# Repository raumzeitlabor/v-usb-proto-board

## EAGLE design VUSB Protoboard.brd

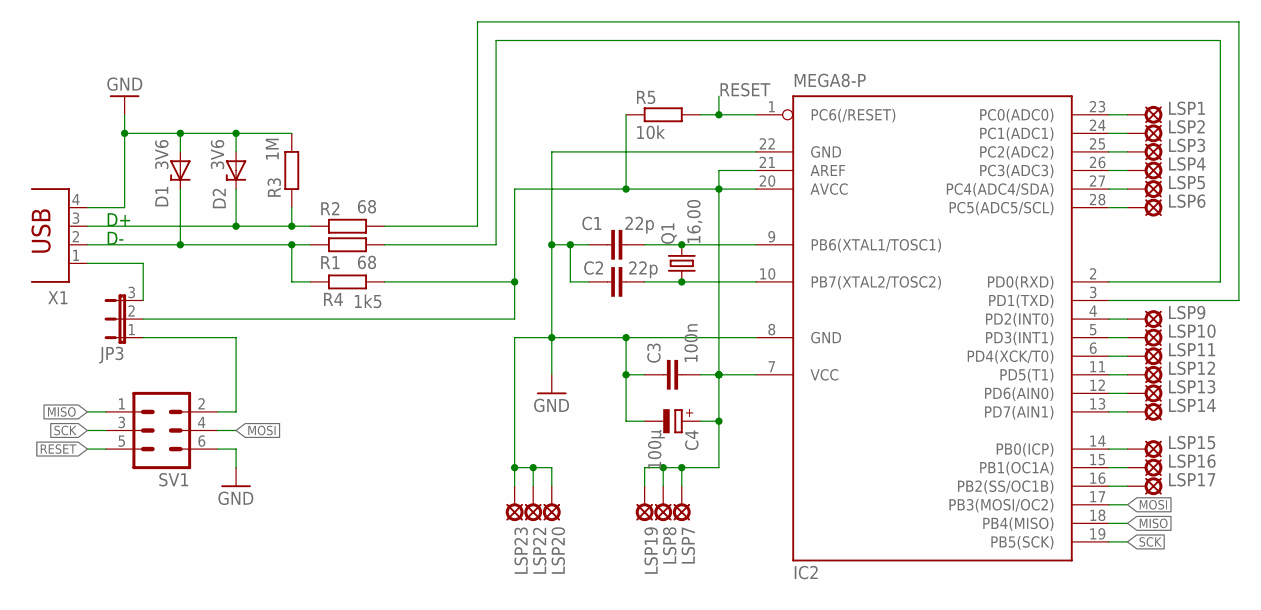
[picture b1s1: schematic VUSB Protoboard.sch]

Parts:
C1, C2: 22p; C025-025X050
C3: 100n; C025-025X050
C4: 100µ; E2,5-6
D1, D2: 3V6; ZDIO-7.5
IC2: MEGA8-P; DIL28-3
JP3: JP2E; JP2
LSP1, LSP2, LSP3, LSP4, LSP5, LSP6, LSP7, LSP8, LSP9, LSP10, LSP11, LSP12, LSP13, LSP14, LSP15, LSP16, LSP17, LSP19, LSP20, LSP22, LSP23: LSP11
Q1: 16,00; HC49/S
R1, R2: 68; 0207/10
R3: 1M; 0207/10
R4: 1k5; 0207/10
R5: 10k; 0207/10
SV1: ML6
X1: PN61729

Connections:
D+: D2.C, R2.1, R3.1, X1.3
D-: D1.C, R1.1, R4.2, X1.2
GND: C1.1, C2.1, C3.1, C4.-, D1.A, D2.A, IC2.8 (GND), IC2.22 (GND), LSP20.MP, LSP22.MP, LSP23.MP, R3.2, SV1.6, X1.4
ISPVCC: JP3.1, SV1.2
MISO: IC2.18 (PB4(MISO)), SV1.1
MOSI: IC2.17 (PB3(MOSI/OC2)), SV1.4
unnamed: IC2.2 (PD0(RXD)), R1.2
unnamed: IC2.3 (PD1(TXD)), R2.2
unnamed: JP3.3, X1.1
unnamed: IC2.16 (PB2(SS/OC1B)), LSP17.MP
unnamed: IC2.15 (PB1(OC1A)), LSP16.MP
unnamed: IC2.14 (PB0(ICP)), LSP15.MP
unnamed: IC2.13 (PD7(AIN1)), LSP14.MP
unnamed: IC2.12 (PD6(AIN0)), LSP13.MP
unnamed: C1.2, IC2.9 (PB6(XTAL1/TOSC1)), Q1.2
unnamed: C2.2, IC2.10 (PB7(XTAL2/TOSC2)), Q1.1
unnamed: IC2.11 (PD5(T1)), LSP12.MP
unnamed: IC2.6 (PD4(XCK/T0)), LSP11.MP
unnamed: IC2.5 (PD3(INT1)), LSP10.MP
unnamed: IC2.4 (PD2(INT0)), LSP9.MP
unnamed: IC2.23 (PC0(ADC0)), LSP1.MP
unnamed: IC2.24 (PC1(ADC1)), LSP2.MP
unnamed: IC2.25 (PC2(ADC2)), LSP3.MP
unnamed: IC2.26 (PC3(ADC3)), LSP4.MP
unnamed: IC2.27 (PC4(ADC4/SDA)), LSP5.MP
unnamed: IC2.28 (PC5(ADC5/SCL)), LSP6.MP
RESET: IC2.1 (PC6(/RESET)), R5.2, SV1.5
SCK: IC2.19 (PB5(SCK)), SV1.3
VCC: C3.2, C4.+, IC2.7 (VCC), IC2.20 (AVCC), IC2.21 (AREF), JP3.2, LSP7.MP, LSP8.MP, LSP19.MP, R4.1, R5.1

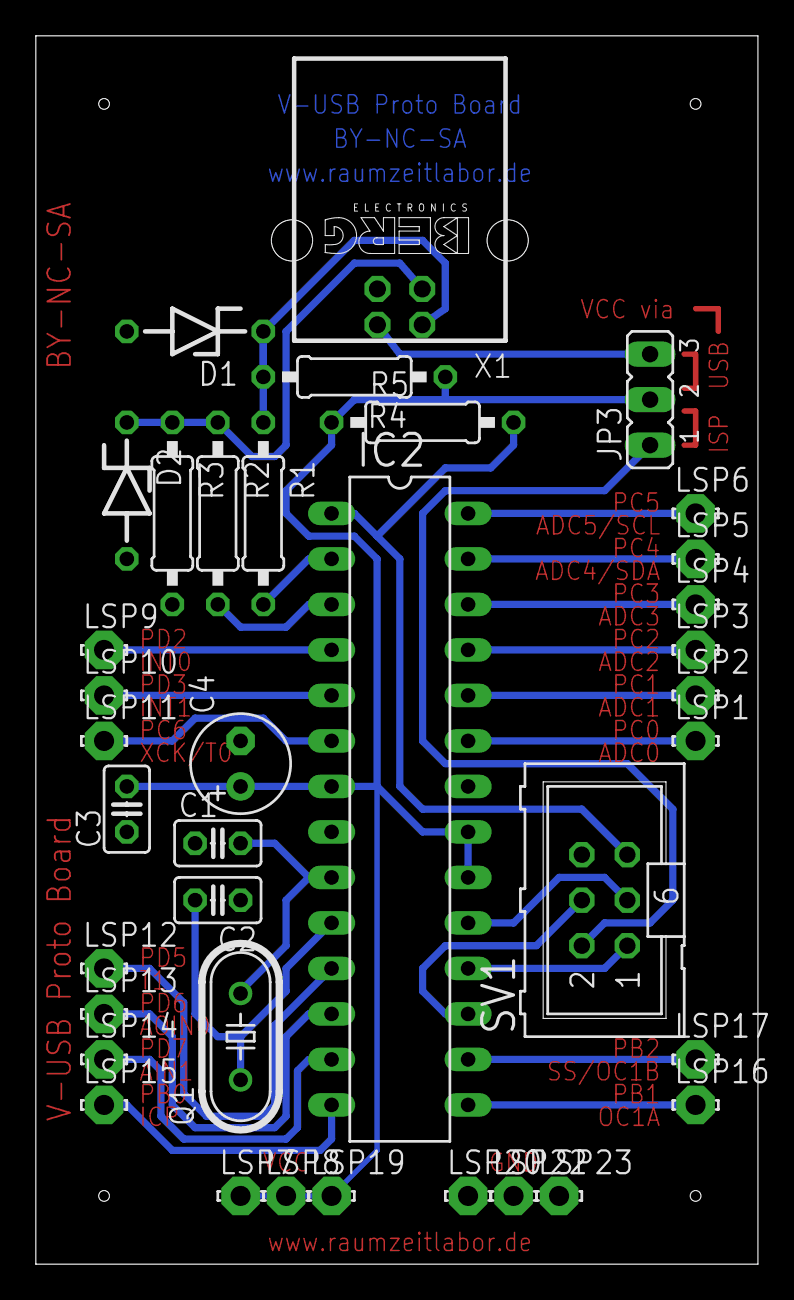
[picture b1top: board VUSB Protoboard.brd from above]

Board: 2 copper layers, 40.3 x 68.6 mm, 37 parts (0 on the bottom side), 29 nets.

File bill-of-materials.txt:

Partlist

Exported from VUSB Protoboard.sch at 10.03.2012 04:17:46

EAGLE Version 6.1.0 Copyright (c) 1988-2012 CadSoft

Assembly variant:

Part     Value          Device            Package      Library        Sheet     Reichelt OrderNo.       Price

C1       22p            C-EU025-025X050   C025-025X050 resistor       1         KERKO 22P               0.06EUR
C2       22p            C-EU025-025X050   C025-025X050 resistor       1         KERKO 22P               0.06EUR
C3       100n           C-EU025-025X050   C025-025X050 resistor       1         MKS-02 100N             0.14EUR
C4       100µ           CPOL-EUE2.5-6     E2,5-6       resistor       1         RAD 100/16              0.04EUR
D1       3V6            ZENER-DIODEZD-7.5 ZDIO-7.5     diode          1         ZF 3,6                  0.05EUR
D2       3V6            ZENER-DIODEZD-7.5 ZDIO-7.5     diode          1         ZF 3,6                  0.05EUR
IC2      MEGA8-P        MEGA8-P           DIL28-3      atmel          1         ATMEGA 8-16 DIP         2.15EUR
JP3                     JP2E              JP2          jumper         1         SL 1X50G 2,54           0.31EUR
Q1       16,00          CRYSTALHC49S      HC49/S       crystal        1         16,0000-HC49U-S         0.17EUR
R1       68             R-EU_0207/10      0207/10      resistor       1         1/4W 60                 0.03EUR
R2       68             R-EU_0207/10      0207/10      resistor       1         1/4W 60                 0.03EUR
R3       1M             R-EU_0207/10      0207/10      resistor       1         1/4W 1,0M               0.03EUR
R4       1k5            R-EU_0207/10      0207/10      resistor       1         1/4W 1,5K               0.03EUR
R5       10k            R-EU_0207/10      0207/10      resistor       1         1/4W 10,0K              0.03EUR
SV1                     ML6               ML6          con-harting-ml 1         WSL 6G                  0.16EUR
X1                      PN61729           PN61729      con-berg       1         USB BW                  0.21EUR

Sum                                                                                                     3.55EUR

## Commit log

2012-03-10 Initial revision
2012-03-10 Added IC Socket
2012-03-11 Changed filled to non-filled pads
